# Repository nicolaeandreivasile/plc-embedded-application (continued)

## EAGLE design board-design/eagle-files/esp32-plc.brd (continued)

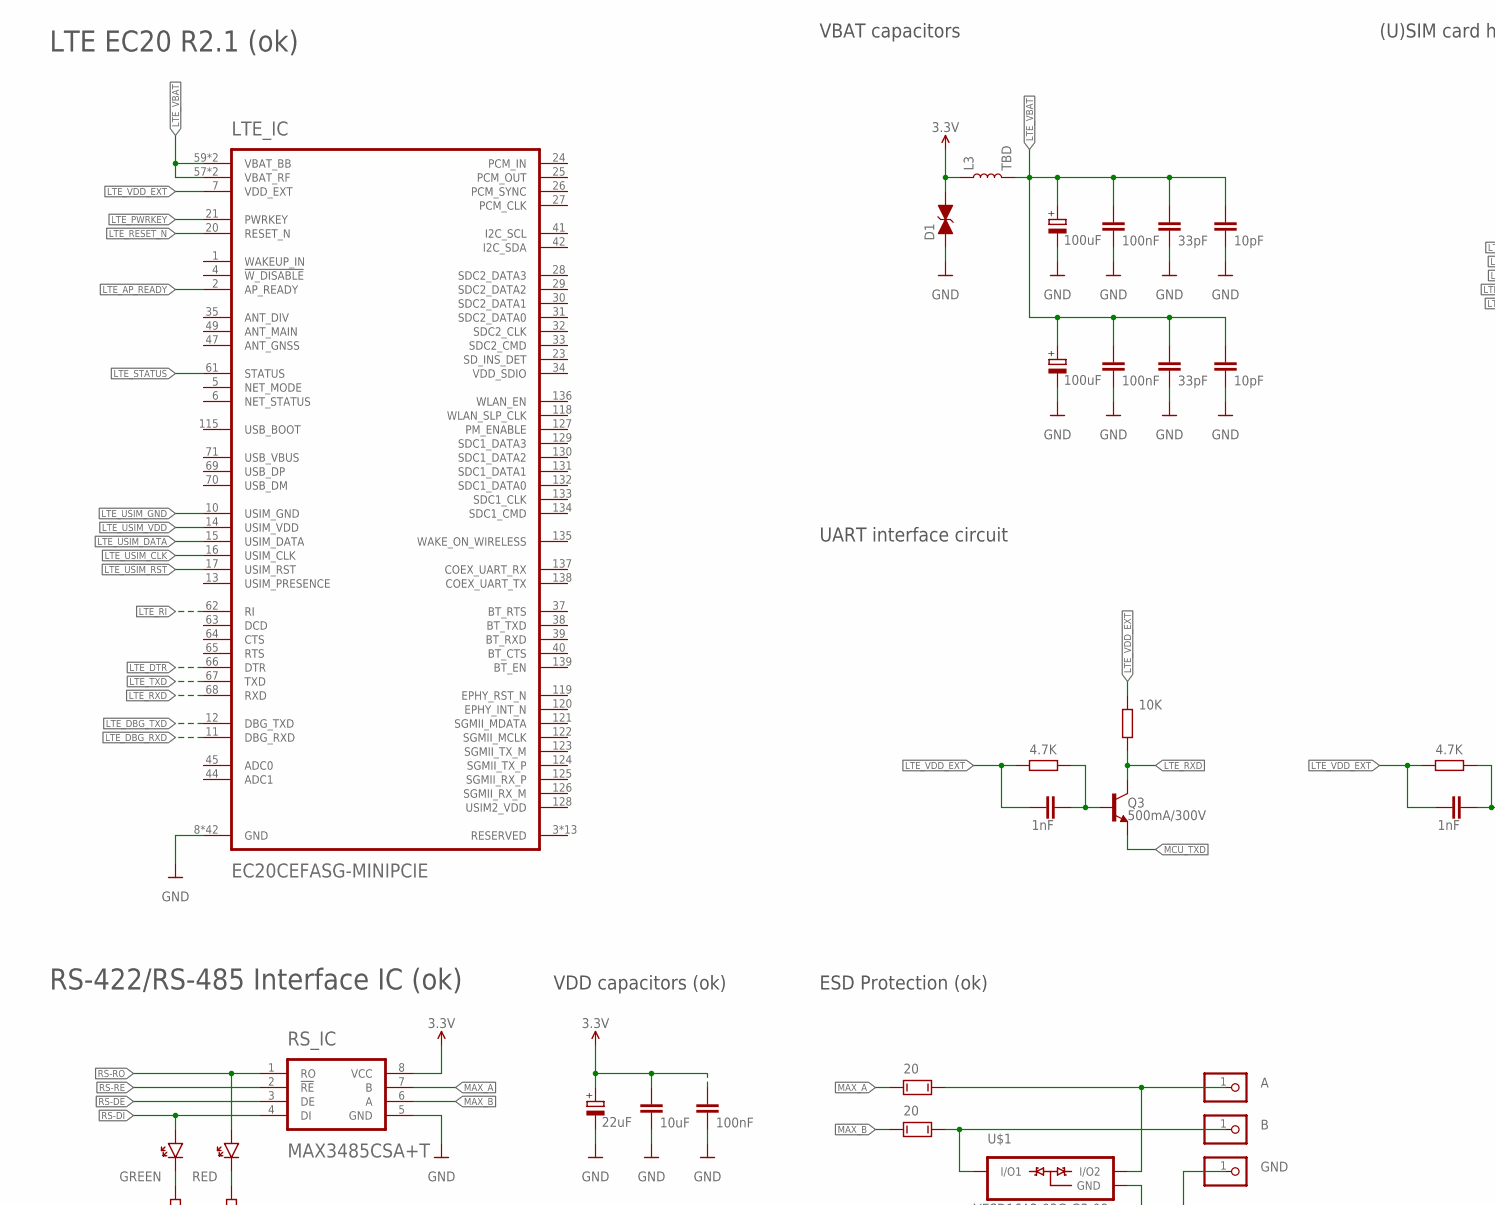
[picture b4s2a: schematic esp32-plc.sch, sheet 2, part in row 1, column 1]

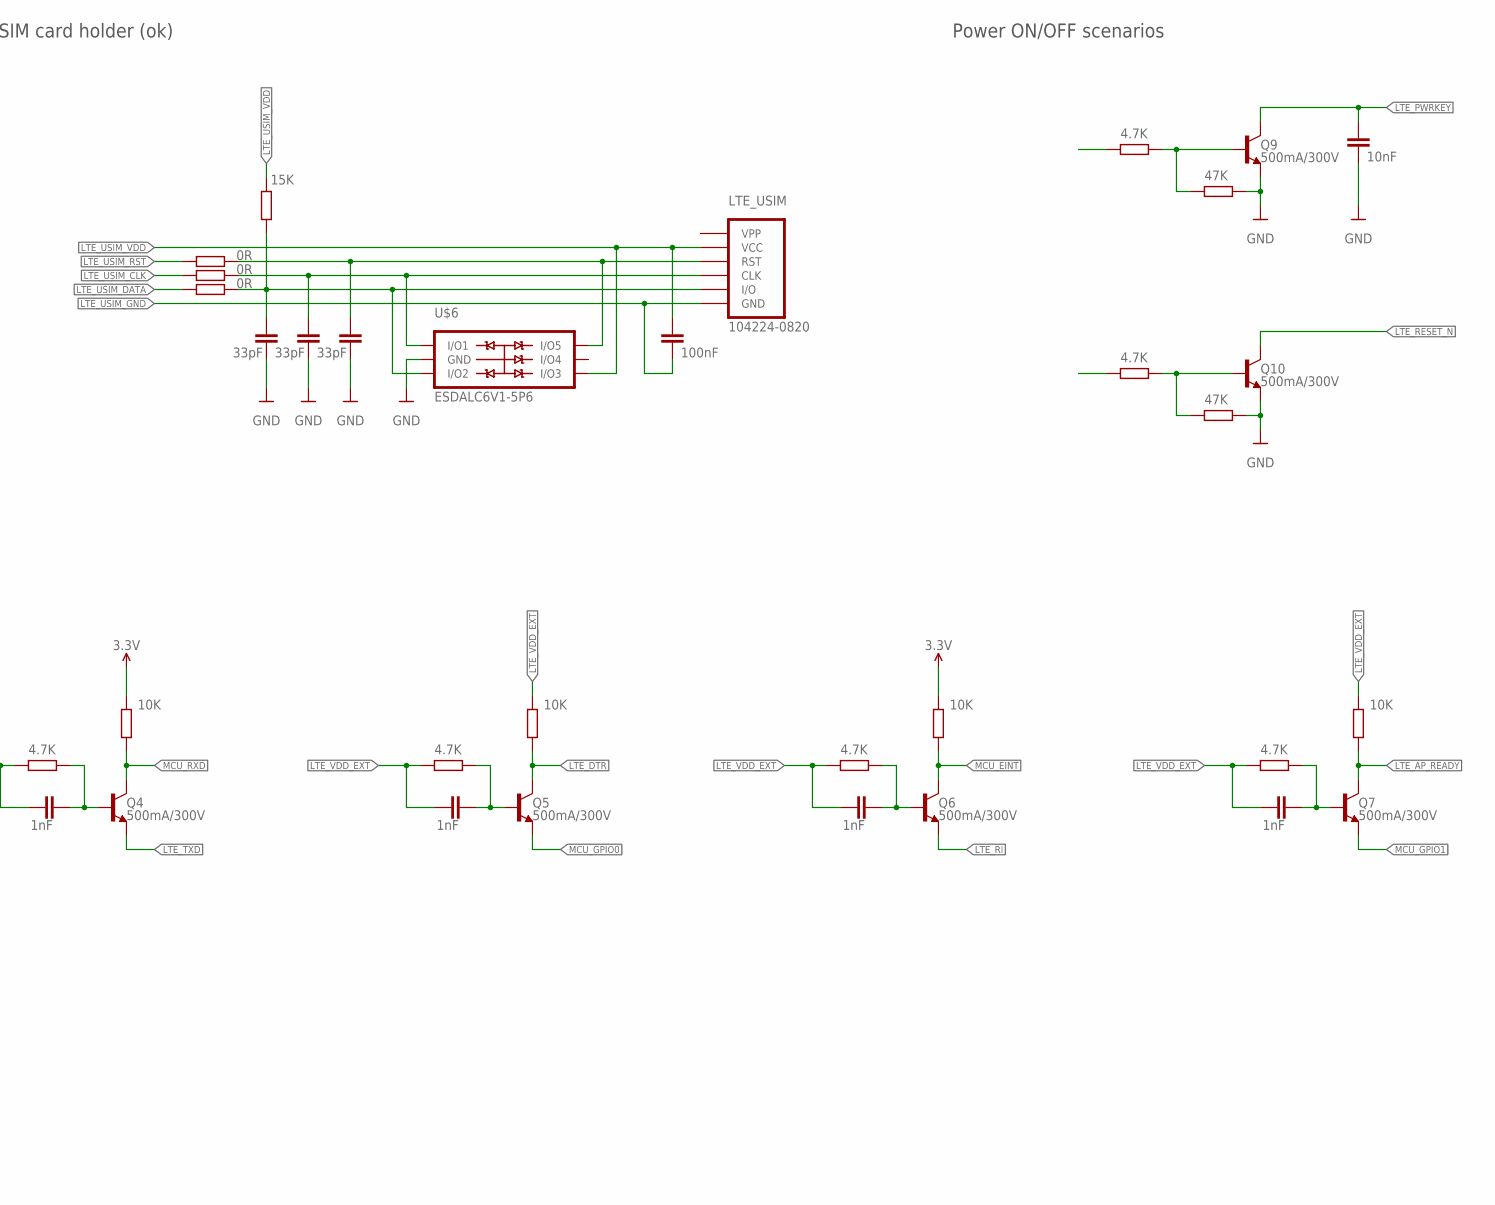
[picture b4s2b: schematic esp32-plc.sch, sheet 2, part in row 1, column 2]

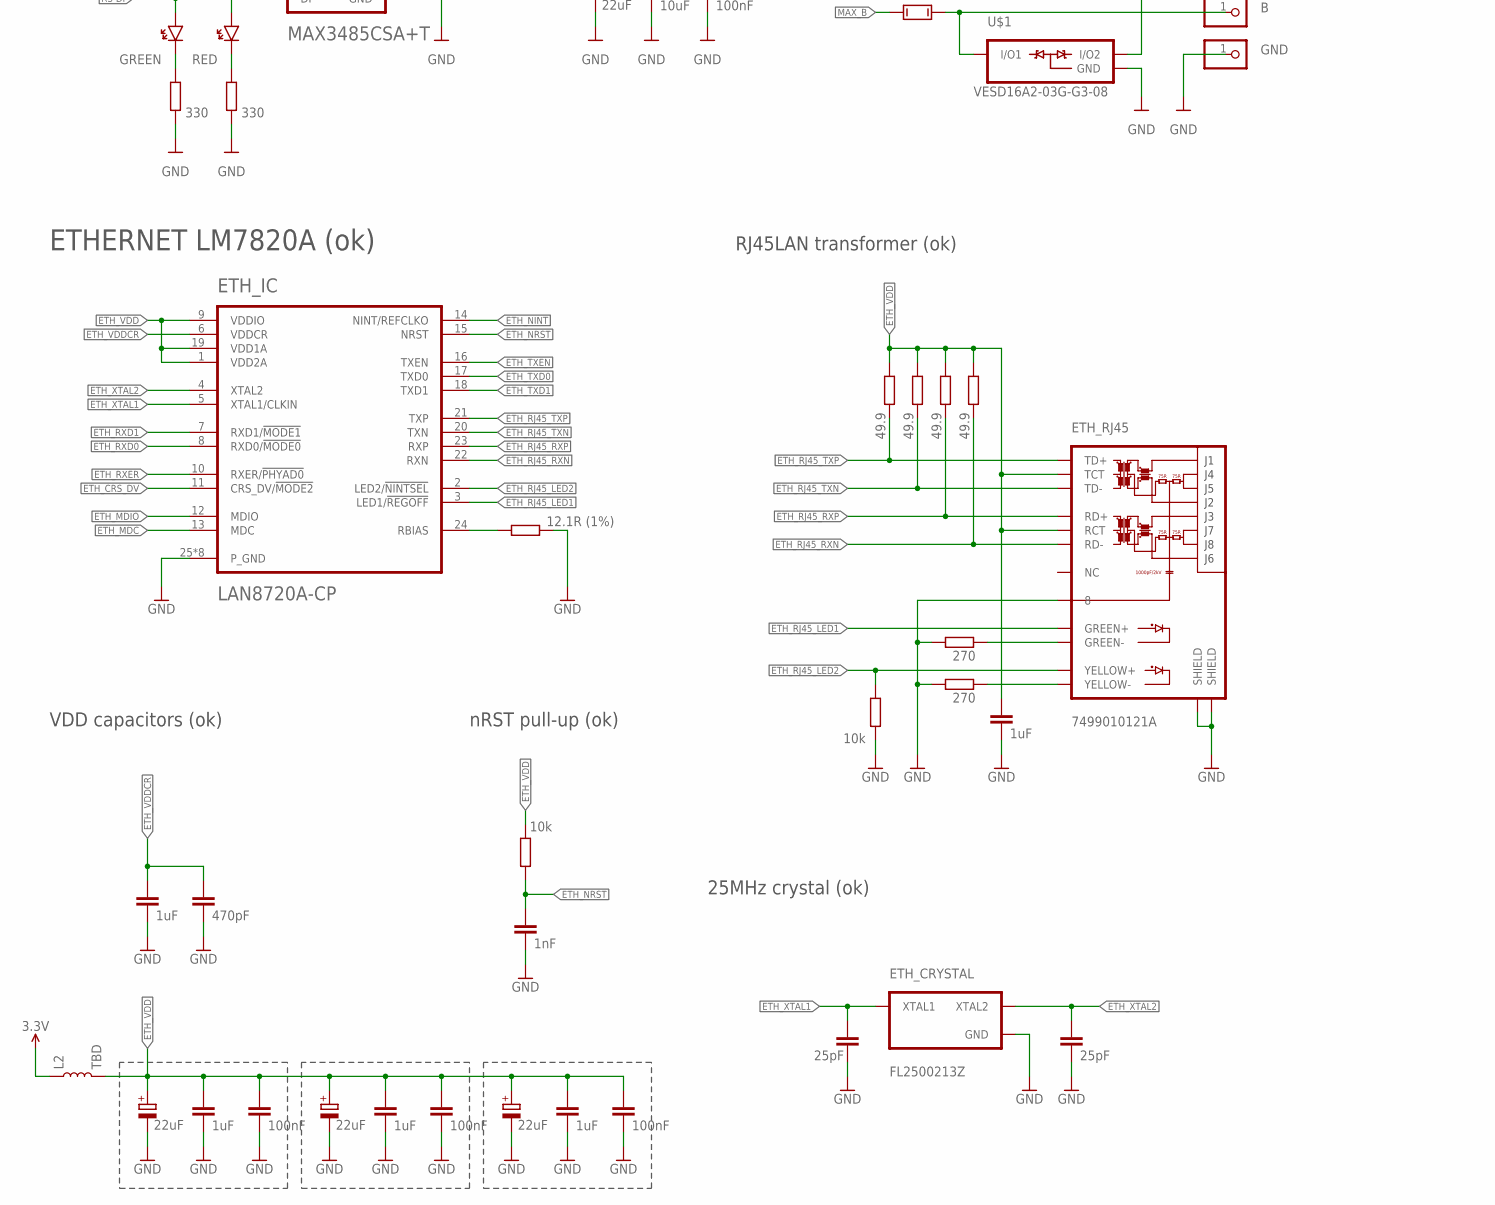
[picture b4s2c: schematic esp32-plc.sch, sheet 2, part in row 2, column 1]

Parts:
D1: 24V; 0603
ETH-C0, ETH-C3, ETH-C6: 22uF; C/6032-28R
ETH-C1, ETH-C4, ETH-C7, ETH-C11: 1uF; C0402
ETH-C2, ETH-C5, ETH-C8: 100nF; C0402
ETH-C10: 470pF; C0402
ETH-C12, ETH-C13: 25pF; C0402
ETH-R0: 12.1R (1%); R0402
ETH-R1: 10k; R0402
ETH-R2, ETH-R3, ETH-R4, ETH-R5: 49.9; R0402
ETH-R6, ETH-R7: 270; R0402
ETH-RJ45-R7, ETH-RJ45-R12: 330; R0402
ETH-RJ45-R11: 10k; R0402
ETH-VDD2A-C5: 1nF; C0402
ETHC-9: 1uF; C0402
ETH_CRYSTAL: FL2500213Z; 3.2X2.5MM
ETH_IC: LAN8720A-CP; QFN-24(4X4MM)
ETH_RJ45: 7499010121A; RJ45-7499010121A
L2, L3: TBD; XFL4020
LTE-UART-R1, LTE-UART-R4, LTE-UART-R6, LTE-UART-R8, LTE-UART-R10: 10K; R0402
LTE-UART-R2, LTE-UART-R3, LTE-UART-R5, LTE-UART-R7, LTE-UART-R9, LTE-UART-R11, LTE-UART-R13: 4.7K; R0402
LTE-UART-R12, LTE-UART-R14: 47K; R0402
LTE-USIM-C1: 100nF; C0402
LTE-USIM-C2, LTE-USIM-C3, LTE-USIM-C4: 33pF; C0402
LTE-USIM-R1: 15K; R0402
LTE-USIM-R2, LTE-USIM-R3, LTE-USIM-R4: 0R; R0402
LTE-VBAT-C1, LTE-VBAT-C5: 100uF; C/6032-28R
LTE-VBAT-C2, LTE-VBAT-C6: 100nF; C0402
LTE-VBAT-C3, LTE-VBAT-C7: 33pF; C0402
LTE-VBAT-C4, LTE-VBAT-C8: 10pF; C0402
LTE-VBAT-C9: 10nF; C0402
LTE-VBAT-C12, LTE-VBAT-C13, LTE-VBAT-C14, LTE-VBAT-C15, LTE-VBAT-C16: 1nF; C0402
LTE_IC: EC20CEFASG-MINIPCIE; EC20-R2.1
LTE_USIM: 104224-0820
MAX_PINH0: A; 1X01
MAX_PINH1: B; 1X01
MAX_PINH2: GND; 1X01
Q3, Q4, Q5, Q6, Q7, Q9, Q10: 500mA/300V; SOT23-3
RS-C0: 22uF; C/6032-28R
RS-C1: 10uF; C0402
RS-C2: 100nF; C0402
RS_IC: MAX3485CSA+T; SOIC-8
U$1: VESD16A2-03G-G3-08; SOT-323-3
U$6: ESDALC6V1-5P6; SOT-666
U$101, U$102: 20; MELF0204
U$139: GREEN; 0603
U$140: RED; 0603

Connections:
3.3V: D1.2 (C), L2.P$1 (1), L3.P$1 (1), LTE-UART-R4.2, LTE-UART-R8.2, RS-C0.+, RS-C1.1, RS-C2.1, RS_IC.8 (VCC); also elsewhere on the board
ETH_CRS_DV: ETH_IC.11 (CRS_DV/!MODE2)
ETH_MDC: ETH_IC.13 (MDC)
ETH_MDIO: ETH_IC.12 (MDIO)
ETH_NINT: ETH_IC.14 (NINT/REFCLKO)
ETH_NRST: ETH-R1.1, ETH-VDD2A-C5.1, ETH_IC.15 (NRST)
ETH_RJ45_LED1: ETH_IC.3 (LED1/!REGOFF), ETH_RJ45.10 (GREEN+)
ETH_RJ45_LED2: ETH-RJ45-R11.2, ETH_IC.2 (LED2/!NINTSEL), ETH_RJ45.12 (YELLOW+)
ETH_RJ45_RXN: ETH-R5.2, ETH_IC.22 (RXN), ETH_RJ45.6 (RD-)
ETH_RJ45_RXP: ETH-R4.2, ETH_IC.23 (RXP), ETH_RJ45.4 (RD+)
ETH_RJ45_TXN: ETH-R3.2, ETH_IC.20 (TXN), ETH_RJ45.3 (TD-)
ETH_RJ45_TXP: ETH-R2.2, ETH_IC.21 (TXP), ETH_RJ45.1 (TD+)
ETH_RXD0: ETH_IC.8 (RXD0/!MODE0)
ETH_RXD1: ETH_IC.7 (RXD1/!MODE1)
ETH_RXER: ETH_IC.10 (RXER/!PHYAD0)
ETH_TXD0: ETH_IC.17 (TXD0)
ETH_TXD1: ETH_IC.18 (TXD1)
ETH_TXEN: ETH_IC.16 (TXEN)
ETH_VDD: ETH-C0.+, ETH-C1.1, ETH-C2.1, ETH-C3.+, ETH-C4.1, ETH-C5.1, ETH-C6.+, ETH-C7.1, ETH-C8.1, ETH-C11.1, ETH-R1.2, ETH-R2.1, ETH-R3.1, ETH-R4.1, ETH-R5.1, ETH_IC.1 (VDD2A), ETH_IC.9 (VDDIO), ETH_IC.19 (VDD1A), ETH_RJ45.2 (TCT), ETH_RJ45.5 (RCT), L2.P$2 (2)
ETH_VDDCR: ETH-C10.1, ETHC-9.1, ETH_IC.6 (VDDCR)
ETH_XTAL1: ETH-C12.1, ETH_CRYSTAL.1 (XTAL1), ETH_IC.5 (XTAL1/CLKIN)
ETH_XTAL2: ETH-C13.1, ETH_CRYSTAL.3 (XTAL2), ETH_IC.4 (XTAL2)
GND: D1.1 (A), ETH-C0.-, ETH-C1.2, ETH-C2.2, ETH-C3.-, ETH-C4.2, ETH-C5.2, ETH-C6.-, ETH-C7.2, ETH-C8.2, ETH-C10.2, ETH-C11.2, ETH-C12.2, ETH-C13.2, ETH-R0.1, ETH-R6.1, ETH-R7.1, ETH-RJ45-R7.2, ETH-RJ45-R11.1, ETH-RJ45-R12.2, ETH-VDD2A-C5.2, ETHC-9.2, ETH_CRYSTAL.2 (GND), ETH_CRYSTAL.4 (GND), ETH_IC.25 (P_GND), ETH_IC.26 (P_GND), ETH_IC.27 (P_GND), ETH_IC.28 (P_GND), ETH_IC.29 (P_GND), ETH_IC.30 (P_GND), ETH_IC.31 (P_GND), ETH_IC.32 (P_GND), ETH_RJ45.8, ETH_RJ45.13 (SHIELD), ETH_RJ45.14 (SHIELD), LTE-UART-R12.1, LTE-UART-R14.1, LTE-USIM-C2.2, LTE-USIM-C3.2, LTE-USIM-C4.2, LTE-VBAT-C1.-, LTE-VBAT-C2.2, LTE-VBAT-C3.2, LTE-VBAT-C4.2, LTE-VBAT-C5.-, LTE-VBAT-C6.2, LTE-VBAT-C7.2, LTE-VBAT-C8.2, LTE-VBAT-C9.2, LTE_IC.8 (GND), LTE_IC.9 (GND), LTE_IC.19 (GND), LTE_IC.22 (GND), LTE_IC.36 (GND), LTE_IC.46 (GND), LTE_IC.48 (GND), LTE_IC.50 (GND), LTE_IC.51 (GND), LTE_IC.52 (GND), LTE_IC.53 (GND), LTE_IC.54 (GND), LTE_IC.56 (GND), LTE_IC.72 (GND), LTE_IC.85 (GND), LTE_IC.86 (GND), LTE_IC.87 (GND), LTE_IC.88 (GND), LTE_IC.89 (GND), LTE_IC.90 (GND), LTE_IC.91 (GND), LTE_IC.92 (GND), LTE_IC.93 (GND), LTE_IC.94 (GND), LTE_IC.95 (GND), LTE_IC.96 (GND), LTE_IC.97 (GND), LTE_IC.98 (GND), LTE_IC.99 (GND), LTE_IC.100 (GND), LTE_IC.101 (GND), LTE_IC.102 (GND), LTE_IC.103 (GND), LTE_IC.104 (GND), LTE_IC.105 (GND), LTE_IC.106 (GND), LTE_IC.107 (GND), LTE_IC.108 (GND), LTE_IC.109 (GND), LTE_IC.110 (GND), LTE_IC.111 (GND), LTE_IC.112 (GND), MAX_PINH2.1, Q9.2 (E), Q10.2 (E), RS-C0.-, RS-C1.2, RS-C2.2, RS_IC.5 (GND), U$1.3 (GND), U$6.2 (GND); also elsewhere on the board
LTE_AP_READY: LTE-UART-R10.1, LTE_IC.2 (AP_READY), Q7.3 (C)
LTE_DBG_RXD: LTE_IC.11 (DBG_RXD)
LTE_DBG_TXD: LTE_IC.12 (DBG_TXD)
LTE_DTR: LTE-UART-R6.1, LTE_IC.66 (DTR), Q5.3 (C)
LTE_PWRKEY: LTE-VBAT-C9.1, LTE_IC.21 (PWRKEY), Q9.3 (C)
LTE_RESET_N: LTE_IC.20 (RESET_N), Q10.3 (C)
LTE_RI: LTE_IC.62 (RI), Q6.2 (E)
LTE_RXD: LTE-UART-R1.1, LTE_IC.68 (RXD), Q3.3 (C)
LTE_TXD: LTE_IC.67 (TXD), Q4.2 (E)
LTE_USIM_CLK: LTE-USIM-R3.2, LTE_IC.16 (USIM_CLK)
LTE_USIM_DATA: LTE-USIM-R2.2, LTE_IC.15 (USIM_DATA)
LTE_USIM_RST: LTE-USIM-R4.2, LTE_IC.17 (USIM_RST)
LTE_VBAT: L3.P$2 (2), LTE-VBAT-C1.+, LTE-VBAT-C2.1, LTE-VBAT-C3.1, LTE-VBAT-C4.1, LTE-VBAT-C5.+, LTE-VBAT-C6.1, LTE-VBAT-C7.1, LTE-VBAT-C8.1, LTE_IC.57 (VBAT_RF), LTE_IC.58 (VBAT_RF), LTE_IC.59 (VBAT_BB), LTE_IC.60 (VBAT_BB)
LTE_VDD_EXT: LTE-UART-R1.2, LTE-UART-R2.2, LTE-UART-R3.2, LTE-UART-R5.2, LTE-UART-R6.2, LTE-UART-R7.2, LTE-UART-R9.2, LTE-UART-R10.2, LTE-VBAT-C12.2, LTE-VBAT-C13.2, LTE-VBAT-C14.2, LTE-VBAT-C15.2, LTE-VBAT-C16.2, LTE_IC.7 (VDD_EXT)
MAX_A: RS_IC.7 (B), U$102.1; also elsewhere on the board
MAX_B: RS_IC.6 (A), U$101.1; also elsewhere on the board
MCU_EINT: LTE-UART-R8.1, Q6.3 (C)
MCU_GPIO0: Q5.2 (E)
MCU_GPIO1: Q7.2 (E)
MCU_RXD: LTE-UART-R4.1, Q4.3 (C)
MCU_TXD: Q3.2 (E)
unnamed: LTE-UART-R5.1, LTE-VBAT-C14.1, Q5.1 (B)
unnamed: LTE-UART-R2.1, LTE-VBAT-C12.1, Q3.1 (B)
unnamed: LTE-UART-R3.1, LTE-VBAT-C13.1, Q4.1 (B)
unnamed: LTE-UART-R9.1, LTE-VBAT-C16.1, Q7.1 (B)
unnamed: LTE-UART-R7.1, LTE-VBAT-C15.1, Q6.1 (B)
unnamed: ETH-RJ45-R7.1, U$139.1
unnamed: ETH-RJ45-R12.1, U$140.1
unnamed: ETH-R6.2, ETH_RJ45.9 (GREEN-)
unnamed: ETH-R7.2, ETH_RJ45.11 (YELLOW-)
unnamed: ETH-R0.2, ETH_IC.24 (RBIAS)
unnamed: LTE-UART-R11.1, LTE-UART-R12.2, Q9.1 (B)
unnamed: LTE-UART-R13.1, LTE-UART-R14.2, Q10.1 (B)
RS-DI: RS_IC.4 (DI), U$139.2; also elsewhere on the board
RS-RO: RS_IC.1 (RO), U$140.2; also elsewhere on the board
USIM_CLK: LTE-USIM-C3.1, LTE-USIM-R3.1, LTE_USIM.S3 (CLK), U$6.1 (I/O1); also elsewhere on the board
USIM_I/O: LTE-USIM-C2.1, LTE-USIM-R1.1, LTE-USIM-R2.1, LTE_USIM.S6 (I/O), U$6.3 (I/O2); also elsewhere on the board
USIM_RST: LTE-USIM-C4.1, LTE-USIM-R4.1, LTE_USIM.S2 (RST), U$6.6 (I/O5); also elsewhere on the board

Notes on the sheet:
LTE EC20 R2.1 (ok)
(U)SIM card holder (ok)
VBAT capacitors
UART interface circuit
RS-422/RS-485 Interface IC (ok)
ETHERNET LM7820A (ok)
VDD capacitors (ok)
nRST pull-up (ok)
25MHz crystal (ok)
RJ45LAN transformer (ok)
ESD Protection (ok)
Power ON/OFF scenarios

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
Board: 2 copper layers, 143 parts (0 on the bottom side), 87 nets, no tracks yet.

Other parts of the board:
U$9: 104224-0820
U$11: MAX3485CSA+T; SOIC-8

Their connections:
3.3V: U$11.8; also elsewhere on the board
GND: U$11.5; also elsewhere on the board
MAX_A: U$11.7; also elsewhere on the board
MAX_B: U$11.6; also elsewhere on the board
RS-DI: U$11.4; also elsewhere on the board
RS-RO: U$11.1; also elsewhere on the board
USIM_CLK: U$9.S3; also elsewhere on the board
USIM_I/O: U$9.S6; also elsewhere on the board
USIM_RST: U$9.S2; also elsewhere on the board

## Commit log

2021-10-17 Initial files added
2021-10-19 Changed board schematic
2021-12-15 Eagle schematic changed
2022-02-09 Added RS485 Interface Module
2022-02-11 Updated schematic
2022-02-13 Logic unit schematic updated
2023-04-20 PLC Update
    Added Ethernet module.
2023-06-25 PLC board design
    Verifications and improvements of the hardware design.
2023-12-02 [UPDATE] Refactored repository
    Updated repository with laatest work. Uploaded work that has been made in EAGLE and continued in Kicad. Removed redundant information.
2023-12-03 [UPDATE]
    Finished ESP32 and ESP32-programmer board designs (few corrections to be made when manufacturer is chosen - design rules).
2023-12-03 [UPDATE]
    Fixed design PDF files.
2023-12-03 [Components]
    Completed component lists for ESP32-programmer and ESP32 boards.
2023-12-08 [FIX]
    Updated footprints for tactile switches.
2023-12-08 [UPDATE]
    Refactored schematic for LTE, Power and other schematic sub-sheets.
2023-12-09 [UPDATE]
    First draft of SAM4E-PLC schematic completed.
2023-12-09 [IN PROGRESS]
    SAM4E-PLC PCB design in progress.
2023-12-10 [UPDATE]
    Work in progress.
2023-12-22 [UPDATE]
    Finished ESP32-PLC board design
2023-12-22 [UPDATE]
    Completed SAM4E-PLC board design.
2023-12-22 [Prototype A completed]
    Completed first board prototype design.
2024-06-04 [PLC implementation]
    Added documentation: datasheets and technical papers.
2024-06-05 [Final report]
    Updated images for documentation.
2024-06-05 [Final report]
    Cleared redundant files.
2024-06-08 [Final report]
    Added simple images for ESP32 adn SAM4
2024-06-11 [Libraries]
    Added used libraries for the KiCad projects.
2024-06-12 [Final report]
    Added 3D models.
2024-06-12 [Documents]
    Fixed documentation.
2024-06-13 [PLC]
    Updated PCB PDFs.
2026-04-05 [Refactor] Documentation refactoring
    Sorted documentation and added final report for the device.
